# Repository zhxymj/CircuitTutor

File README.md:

# 智绘电路 · CircuitTutor

> 用中文描述电路需求，在本机生成可编辑的原理图，再用确定性门禁（ERC / 额定值 / ngspice / KiCad 官方 ERC）复验，最后导出 SVG、BOM、SPICE、KiCad 工程与 PCB 候选。

当前产品版本：1.6.0。

<sub>窄屏布局：</sub> 

---

## 这是什么

一个**本地优先**的电路设计助手。左侧用中文描述需求（或粘贴图片、TSX 代码、外部工具结果），中间得到一张可拖动、可改参、可连线、可撤销的真实原理图，右侧看到真实元件属性与校验结果，底部可查生成过程与检查明细。

它不追求"AI 说什么就是什么"：**生成的候选必须经过确定性门禁才能被接受**，未运行的工具会如实显示"未完成"，而不是当作通过。

## 核心能力

- **中文需求 → 电路**：152 类元件目录、40 个内置模板与本地匹配器，缺供电、缺 I2C 地址等关键条件时先向你澄清。
- **真实可编辑原理图**：鼠标选中、拖动、引脚连线、缩放、改参数、撤销（Ctrl+Z），参数修改进入真实撤销栈。
- **确定性电气校验**：33 条 ERC 规则（短路、悬空、极性、LED 缺限流、缺去耦等）+ 额定值核对，不是模型自评。
- **外部工具复验**：本机 ngspice 跑 SPICE（op/ac/tran/dc），KiCad 官方 CLI 跑 ERC 与网表比对，导出完整 KiCad 工程。
- **教学时序图**：教学模式下的瞬态时序图由真实 `.tran` 输出绘制，并标注阈值与采样行数。
- **多入口生成**：图片识别（本机 CircuitVision）、代码建电路（tscircuit TSX）、外部结果导入（CircuitVision / HCD / tscircuit）。
- **分组导出**：原理图与物料（SVG / BOM / KiCad）、SPICE 仿真、PCB 与制造候选。
- **教学模式**：术语解释气泡、学习路径（需求→生成→审核→校验→导出）、门禁"为什么查这项"、新手引导与元件教学卡；默认关闭，只影响呈现，不改变电路与校验结果。

## 快速开始

需要 **Python 3.10+**，仅此而已。运行时零第三方依赖，无需 `pip install`。

```bash
git clone https://github.com/zhxymj/CircuitTutor.git
cd CircuitTutor
python server.py
```

然后打开 <http://127.0.0.1:8765/>。Windows 上也可以直接双击 `启动演示.bat`。

用 Docker：

```bash
docker compose up --build
```

### 可选：接入在线大模型

不配 Key 也能完整跑通——匹配到模板的需求会走本地离线路径。想用在线模型生成（自由需求、增量改图）：

```bash
cp .env.template .env
# 在 .env 中填入 DEEPSEEK_API_KEY
```

### 可选：启用外部工具复验

装了 `kicad-cli` 与 `ngspice` 后，对应的门禁会真正执行并给出官方结论；没装则如实显示"未完成"。

```bash
export KICAD_CLI_PATH=/path/to/kicad-cli
export NGSPICE_PATH=/path/to/ngspice
```

### 可选：使用本地微调权重（研究用途）

默认加载工具链里的上游公开权重。若已用 `tools/train_yolo_detector.py` 完成本地训练，可登记为可选权重：

```bash
python tools/install_local_model.py --run evidence/yolo_training/round4_warmstart50
python tools/vision_detect.py --input path/to/image.png --model local
```

- `CIRCUIT_VISION_MODEL`：`upstream`（默认）或 `local`。
- `CIRCUIT_VISION_LOCAL_MODEL_ROOT`：本地权重目录，默认工具链 `vision-models/hcd-local`。
- 缺权重、哈希不符或类别不符会直接停止推理，不会静默回退到上游权重。
- 本地权重只支持 `resistor` 与 `capacitor.unpolarized` 两类，其余符号不会被检测；权重不随仓库分发，仅限研究评估。

## 配置

全部通过环境变量或 `.env` 配置，默认值如下（与 `core/config.py` 一致）：

| 变量 | 默认 | 说明 |
|---|---|---|
| `LSQC_HOST` | `127.0.0.1` | 监听地址；仅本机可访问 |
| `LSQC_PORT` | `8765` | 监听端口 |
| `DEEPSEEK_API_KEY` | `（空）` | 未配置时只走本地模板，不调用在线模型 |
| `LLM_TIMEOUT_S` | `90` | 单次模型调用超时（秒） |
| `LLM_RETRIES` | `2` | 模型调用失败重试次数 |
| `LLM_STRUCT_RETRIES` | `2` | 结构化输出重试次数 |
| `LLM_ERC_RETRIES` | `1` | 带 ERC 反馈的重试次数 |
| `LLM_BUDGET` | `5` | 单次生成允许的模型调用预算 |
| `LLM_MAX_TOKENS` | `4096` | 单次响应最大 token |
| `MAX_QUERY_LEN` | `500` | 需求文本最大长度 |
| `KICAD_CLI_TIMEOUT_S` | `90` | 单次 KiCad CLI 超时（秒） |
| `KICAD_CLI_PATH` | `（自动探测）` | 未设置时在 PATH 与工具链中查找 |
| `NGSPICE_PATH` | `（自动探测）` | 未设置时在 PATH 与工具链中查找 |
| `LSQC_RATE_LIMIT` | `30` | 每 IP 每分钟 LLM 端点请求上限，`0` 关闭 |
| `LSQC_KICAD_RATE_LIMIT` | `20` | 每 IP 每分钟 KiCad 端点请求上限 |
| `LSQC_SSE_HEARTBEAT_S` | `15` | SSE 心跳间隔（秒） |
| `LSQC_LOG_LEVEL` | `INFO` | 日志级别 |

**端口回退**：若未设置 `LSQC_PORT`，但环境里存在标准变量 `PORT`（部分云平台会自动注入），服务会采用它并绑定 `0.0.0.0:PORT`。`PORT` 是外部环境变量名，与内部解析后的端口常量同名不同义，因此不列入上表。

## 项目结构

```
智绘电路/
├── server.py            # 标准库 HTTP 服务与全部 API 路由
├── core/                # 领域逻辑：目录、模板、ERC、SPICE、KiCad、PCB、集成桥
├── web/                 # 原生 JS 前端（无构建步骤、无框架）
├── tests/               # 测试套件与统一跑测入口
├── tools/               # 构建、归档、工具链激活等脚本
├── docs/                # 用户手册、API、架构与说明文档
├── data/                # 少量运行所需数据与示例
└── third_party/         # 第三方来源归因（见下）
```

## 测试

统一入口是 `tests/run_tests.py`，按能力分组：

```bash
python tests/run_tests.py --profile fast      # 快速核心
python tests/run_tests.py --profile eda       # 电气/EDA 相关
python tests/run_tests.py --profile release   # 交付打包（需本地 7-Zip）
python tests/run_tests.py --profile all       # 全部
```

前端为原生 JS，相关契约由 Node 测试覆盖：

```bash
node tests/test_frontend.js
node tests/test_workbench_ui.js
```

> 部分验收套件依赖本地归档证据（`evidence/`，体积很大且不入库），在全新克隆上会跳过或不可用；核心与 EDA 套件不依赖它。

## 架构

前端原生 JS ↔ 标准库 HTTP 服务 ↔ 领域模块（目录/模板/ERC/SPICE/KiCad/PCB）↔ 外部工具桥（ngspice、kicad-cli、tscircuit、CircuitVision）。

生成链路是分阶段的：**中文需求 → 澄清 → 候选电路 → 全目录结构校验 → 电气门禁 → 人工审核 → 应用/编辑/撤销**。每个阶段的产物与结论分开记录，模板回退不记为 AI 生成成功，预览完成不等于通过电气验收。

细节见 [docs/作品说明书.md](docs/作品说明书.md)、[docs/架构-生成精确性.svg](docs/架构-生成精确性.svg) 与 [docs/API.md](docs/API.md)。

## 为什么不夸大

- 制造类输出始终 `manufacturing_release=false`，需电子工程师与板厂复核。
- 未安装或未运行的工具显示"未完成"，不以估算替代结论。
- 图片识别与几何候选都需要人工确认器件、数值与引脚网络，交叉点不会自动成为电气网络。
- 教学时序图来自真实仿真输出，但阈值数字化会丢失模拟细节，不是实测波形。

## 第三方与许可

本项目自身以 **MIT** 许可发布，见 [LICENSE](LICENSE)。同时复用了若干开源项目，各自的来源、固定版本与许可事实记录在 [docs/开源项目集成.md](docs/开源项目集成.md) 与 `third_party/`：

| 上游 | 用途 | 许可 |
|---|---|---|
| [tscircuit](https://github.com/tscircuit/tscircuit) | 代码（TSX）建电路 | MIT / ISC |
| [CircuitVision](https://github.com/JKc66/CircuitVision) | 本机图片识别 | Apache-2.0 |
| [HCD](https://github.com/wanghaoyu6661/Hand-Drawn-Circuit-Diagram-Recognition) | 手绘几何候选（6 个算法） | **根许可证未明确**，仅本地/私有使用，不声明为可再分发 |
| [wavedrom](https://github.com/wavedrom/wavedrom) | 教学瞬态时序图渲染 | MIT |
| KiCad 官方库与 CLI | ERC / DRC / 封装 | 库 CC BY-SA 4.0；CLI GPL |
| ngspice | SPICE 仿真 | 见上游 |

上游源码快照中的大体积部分（`third_party/upstream/CircuitVision`、`third_party/upstream/HCD`）保留在本地但不入库。逐项文件哈希与边界说明见 [third_party/](third_party/) 下的归因文件。

## 贡献

欢迎提交 issue 与 PR，请先阅读 [CONTRIBUTING.md](CONTRIBUTING.md)。安全问题请按 [SECURITY.md](SECURITY.md) 私下报告。

## 文档索引

| 文档 | 内容 |
|---|---|
| [用户手册](docs/用户手册.md) | 界面操作与常见流程 |
| [API](docs/API.md) | 全部 HTTP 接口与参数 |
| [作品说明书](docs/作品说明书.md) | 系统设计与实现说明 |
| [开源项目集成](docs/开源项目集成.md) | 第三方来源、许可与边界 |
| [演示说明](docs/演示说明.md) | 建议演示顺序 |
| [交付与验收记录](docs/交付与验收记录.md) | 历史交付与验收记录（归档） |

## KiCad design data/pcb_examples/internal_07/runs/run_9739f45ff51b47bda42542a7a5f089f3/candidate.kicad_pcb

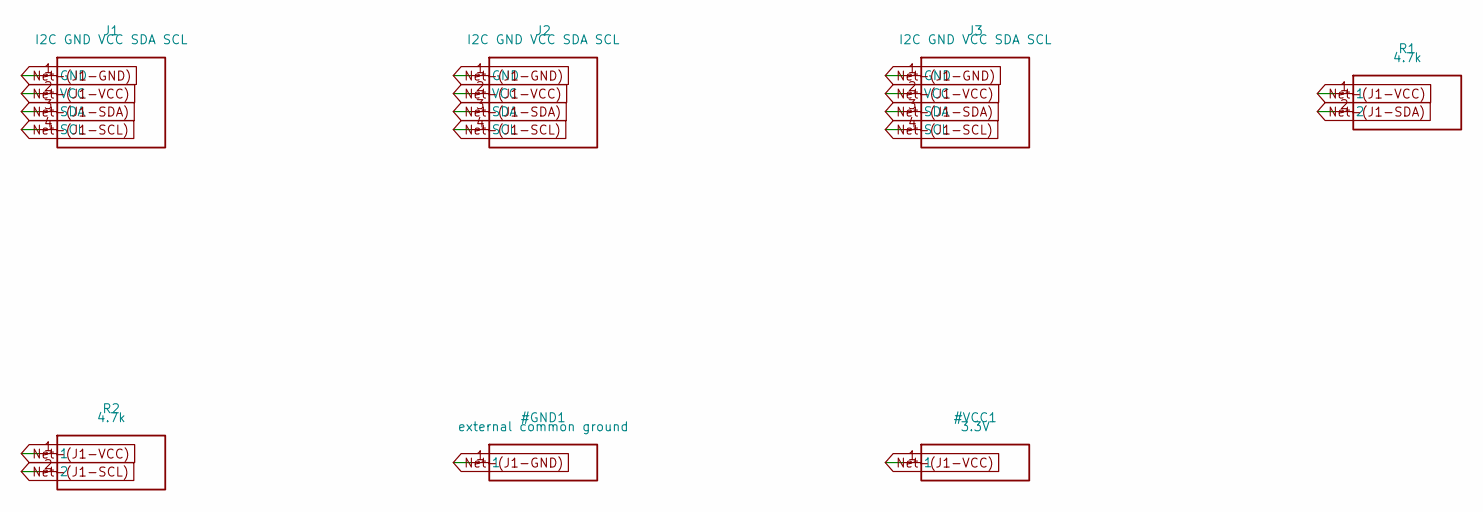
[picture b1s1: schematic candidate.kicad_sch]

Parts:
J1, J2, J3: I2C GND VCC SDA SCL; PinHeader_1x04_P2.54mm_Vertical; MPN TSW-104-07-G-S
R1, R2: 4.7k; R_0805_2012Metric; MPN RC0805FR-074K7L

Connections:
unnamed: J1.1 (GND), J2.1 (GND), J3.1 (GND)
unnamed: J1.4 (SCL), J2.4 (SCL), J3.4 (SCL), R2.2
unnamed: J1.3 (SDA), J2.3 (SDA), J3.3 (SDA), R1.2
unnamed: J1.2 (VCC), J2.2 (VCC), J3.2 (VCC), R1.1, R2.1

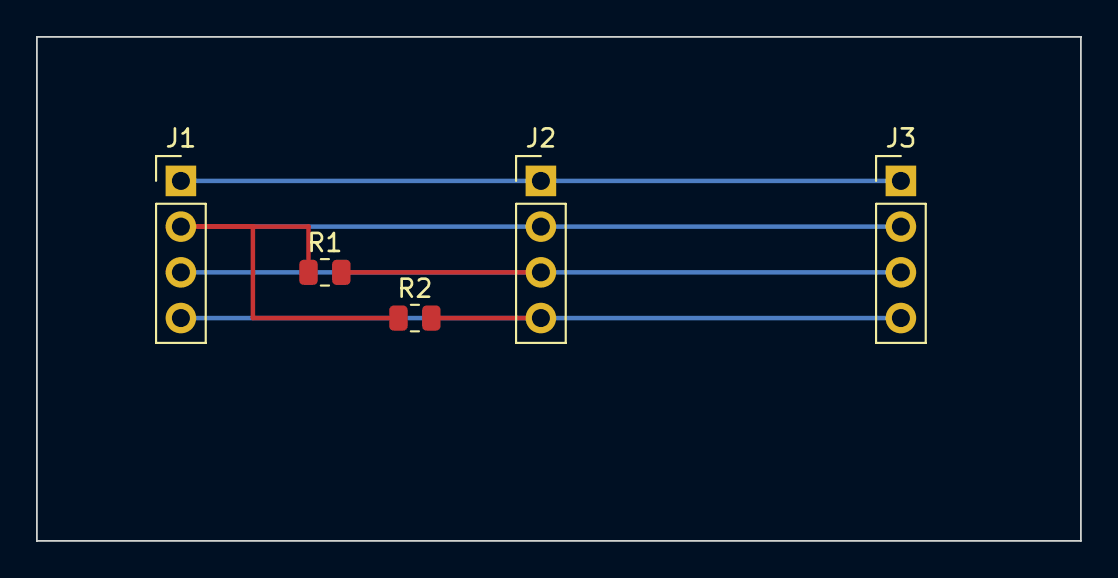
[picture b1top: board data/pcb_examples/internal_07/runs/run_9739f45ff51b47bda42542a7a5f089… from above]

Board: 2 copper layers, 58.0 x 28.0 mm, 5 parts (0 on the bottom side), 4 nets.

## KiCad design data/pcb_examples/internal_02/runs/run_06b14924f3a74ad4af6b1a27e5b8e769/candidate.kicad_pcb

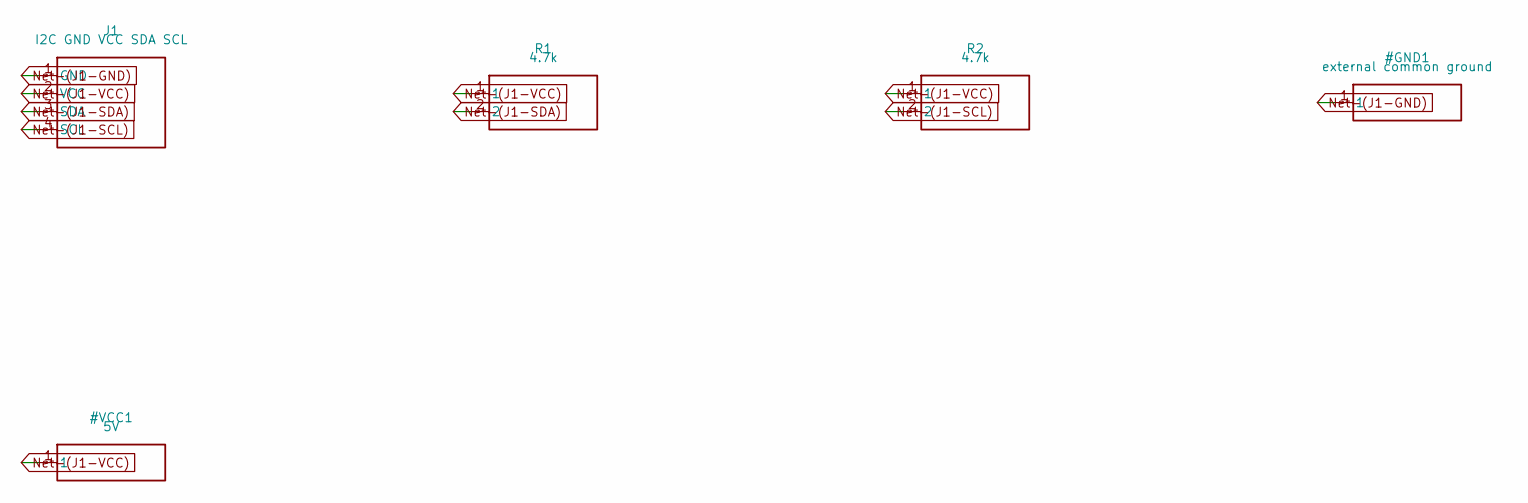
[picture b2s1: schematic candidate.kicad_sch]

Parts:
J1: I2C GND VCC SDA SCL; PinHeader_1x04_P2.54mm_Vertical; MPN TSW-104-07-G-S
R1, R2: 4.7k; R_0805_2012Metric; MPN RC0805FR-074K7L

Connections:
unnamed: J1.4 (SCL), R2.2
unnamed: J1.3 (SDA), R1.2
unnamed: J1.2 (VCC), R1.1, R2.1

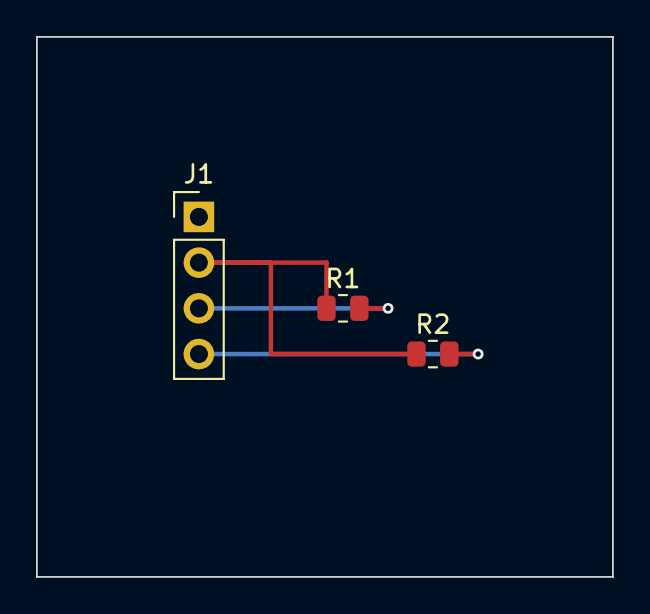
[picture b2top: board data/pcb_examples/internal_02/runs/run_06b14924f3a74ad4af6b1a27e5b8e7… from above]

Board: 2 copper layers, 32.0 x 30.0 mm, 3 parts (0 on the bottom side), 3 nets.

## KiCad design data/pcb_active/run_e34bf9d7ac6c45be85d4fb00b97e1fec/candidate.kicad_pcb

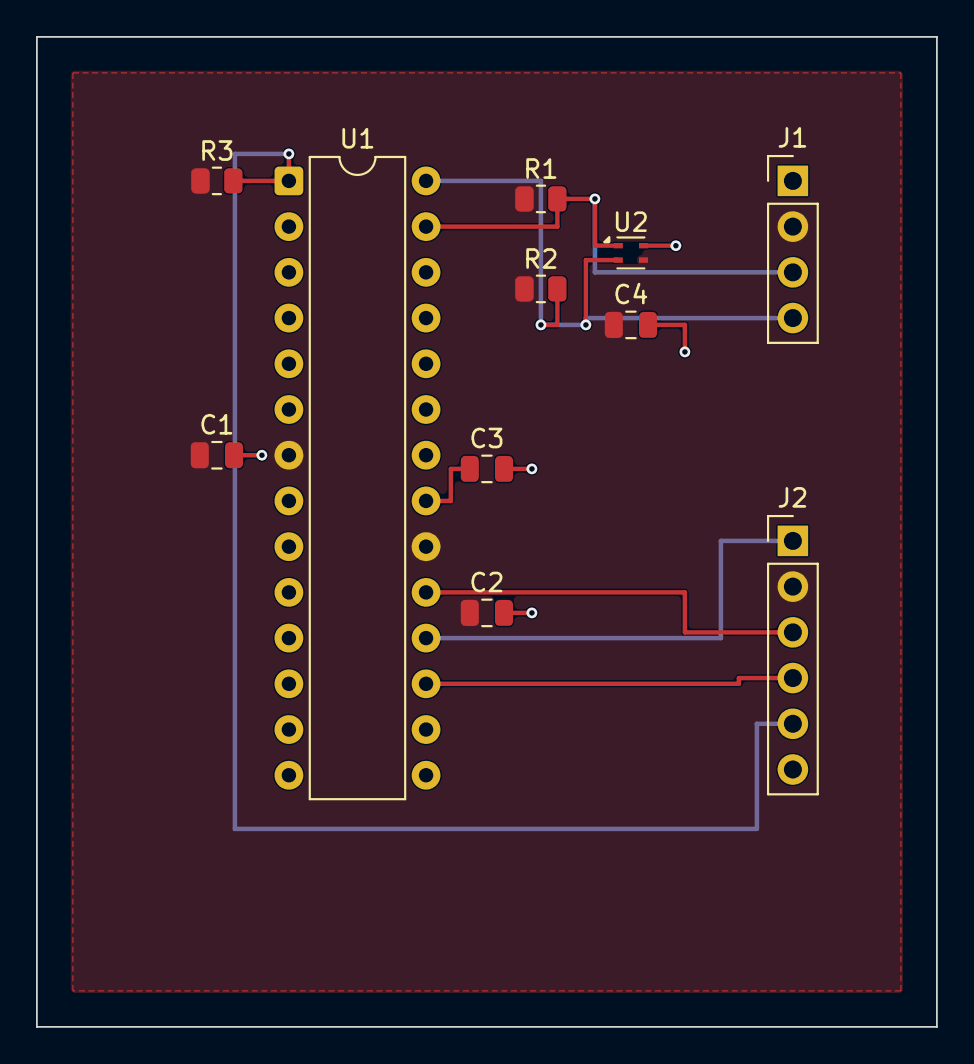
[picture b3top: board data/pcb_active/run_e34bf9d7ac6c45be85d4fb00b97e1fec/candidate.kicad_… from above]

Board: 2 copper layers, 50.0 x 55.0 mm, 11 parts (0 on the bottom side), 9 nets.

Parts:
C1, C2, C3, C4: 100nF; C_0805_2012Metric
J1: I2C GND VCC SDA SCL; PinHeader_1x04_P2.54mm_Vertical
J2: CUSTOM ISP MISO VCC SCK MOSI RESET GND; PinHeader_1x06_P2.54mm_Vertical
R1, R2: 4.7k; R_0805_2012Metric
R3: 10k; R_0805_2012Metric
U1: ATmega328P-PU; DIP-28_W7.62mm
U2: SHT41-AD1B; Sensirion_DFN-4_1.5x1.5mm_P0.8mm_SHT4x_NoCentralPad

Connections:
unnamed: C1.1, C2.1, C4.1, J1.2, J2.2, R1.1, R2.1, R3.1, U1.7, U1.20, U2.3
unnamed: C1.2, C2.2, C3.2, C4.2, J1.1, J2.6, U1.8, U1.22, U2.4
unnamed: C3.1, U1.21
unnamed: J1.4, R2.2, U1.28, U2.2
unnamed: J1.3, R1.2, U1.27, U2.1
unnamed: J2.5, R3.2, U1.1
unnamed: J2.1, U1.18
unnamed: J2.4, U1.17
unnamed: J2.3, U1.19

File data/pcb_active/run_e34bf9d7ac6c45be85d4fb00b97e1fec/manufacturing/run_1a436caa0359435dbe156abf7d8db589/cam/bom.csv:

Reference,Value,MPN,Manufacturer,Footprint,Datasheet
U1,ATmega328P-PU,ATMEGA328P-PU,Microchip,Package_DIP:DIP-28_W7.62mm,https://ww1.microchip.com/downloads/aemDocuments/documents/M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
U2,SHT41-AD1B,SHT41-AD1B-R2,Sensirion,Sensor_Humidity:Sensirion_DFN-4_1.5x1.5mm_P0.8mm_SHT4x_NoCentralPad,https://sensirion.com/media/documents/33FD6951/624C4357/Data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
J1,I2C GND VCC SDA SCL,TSW-104-07-G-S,Samtec,Connector_PinHeader_2.54mm:PinHeader_1x04_P2.54mm_Vertical,https://www.samtec.com/products/tsw-104-07-g-s
J2,CUSTOM ISP MISO VCC SCK MOSI RESET GND,TSW-106-07-G-S,Samtec,Connector_PinHeader_2.54mm:PinHeader_1x06_P2.54mm_Vertical,https://www.samtec.com/products/tsw-106-07-g-s
R1,4.7k,RC0805FR-074K7L,YAGEO,Resistor_SMD:R_0805_2012Metric,https://www.yageogroup.com/component-documentation/download/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
R2,4.7k,RC0805FR-074K7L,YAGEO,Resistor_SMD:R_0805_2012Metric,https://www.yageogroup.com/component-documentation/download/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
R3,10k,RC0805FR-0710KL,YAGEO,Resistor_SMD:R_0805_2012Metric,https://www.yageogroup.com/component-documentation/download/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
C1,100nF,GRM21BR71H104KA01L,Murata,Capacitor_SMD:C_0805_2012Metric,https://search.murata.co.jp/Ceramy/image/img/A01X/G101/ENG/G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
C2,100nF,GRM21BR71H104KA01L,Murata,Capacitor_SMD:C_0805_2012Metric,https://search.murata.co.jp/Ceramy/image/img/A01X/G101/ENG/G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
C3,100nF,GRM21BR71H104KA01L,Murata,Capacitor_SMD:C_0805_2012Metric,https://search.murata.co.jp/Ceramy/image/img/A01X/G101/ENG/G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
C4,100nF,GRM21BR71H104KA01L,Murata,Capacitor_SMD:C_0805_2012Metric,https://search.murata.co.jp/Ceramy/image/img/A01X/G101/ENG/G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

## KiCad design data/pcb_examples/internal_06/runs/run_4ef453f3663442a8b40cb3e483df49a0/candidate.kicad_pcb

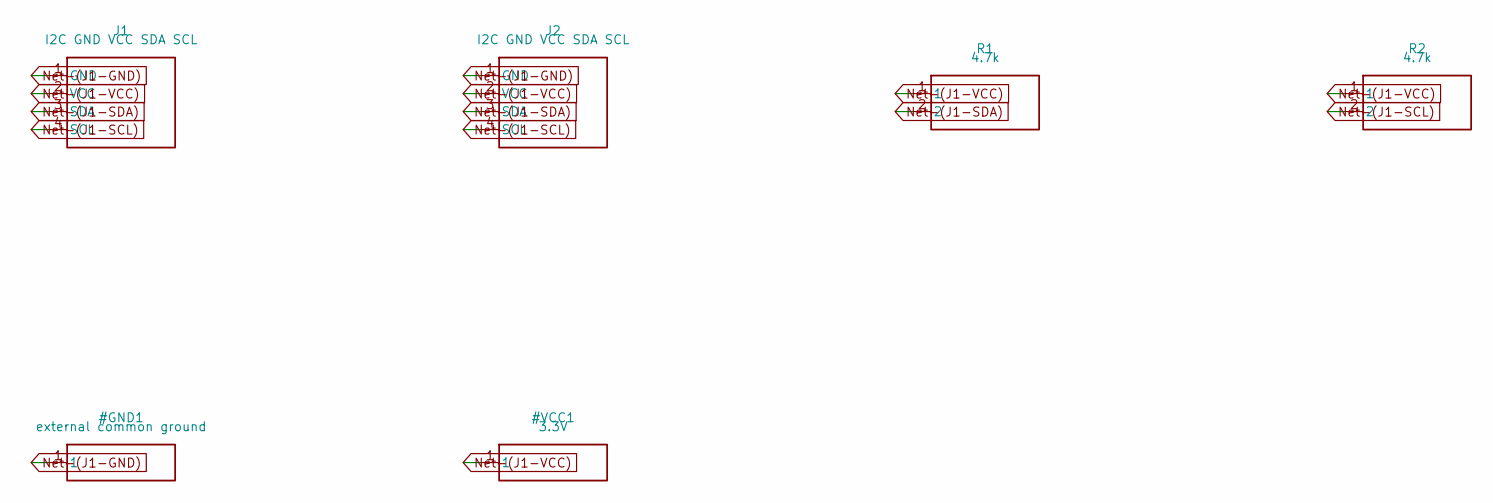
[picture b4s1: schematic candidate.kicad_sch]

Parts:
J1, J2: I2C GND VCC SDA SCL; PinHeader_1x04_P2.54mm_Vertical; MPN TSW-104-07-G-S
R1, R2: 4.7k; R_0805_2012Metric; MPN RC0805FR-074K7L

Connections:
unnamed: J1.1 (GND), J2.1 (GND)
unnamed: J1.4 (SCL), J2.4 (SCL), R2.2
unnamed: J1.3 (SDA), J2.3 (SDA), R1.2
unnamed: J1.2 (VCC), J2.2 (VCC), R1.1, R2.1

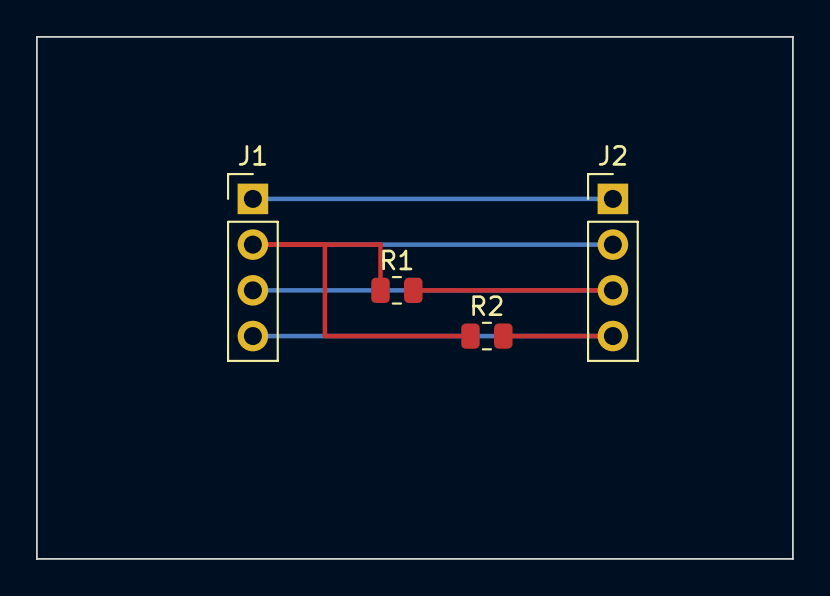
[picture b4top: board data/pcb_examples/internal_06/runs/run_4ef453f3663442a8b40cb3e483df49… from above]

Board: 2 copper layers, 42.0 x 29.0 mm, 4 parts (0 on the bottom side), 4 nets.

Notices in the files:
README.md:
License: MIT
